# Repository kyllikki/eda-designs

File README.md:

EDA Designs
===========

Electronic designs under MIT licence unless stated differently in their directories.

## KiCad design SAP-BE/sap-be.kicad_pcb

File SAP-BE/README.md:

Simple As Possible (SAP) computer by Ben Eater
==============================================

This is a schematic capture of this project derived from the excellent video series [1]

The design belongs to Ben, I just made a schematic in kicad

This schematic is released under CC BY-SA licence

[1] https://www.youtube.com/watch?v=HyznrdDSSGM&list=PLowKtXNTBypGqImE405J2565dvjafglHU

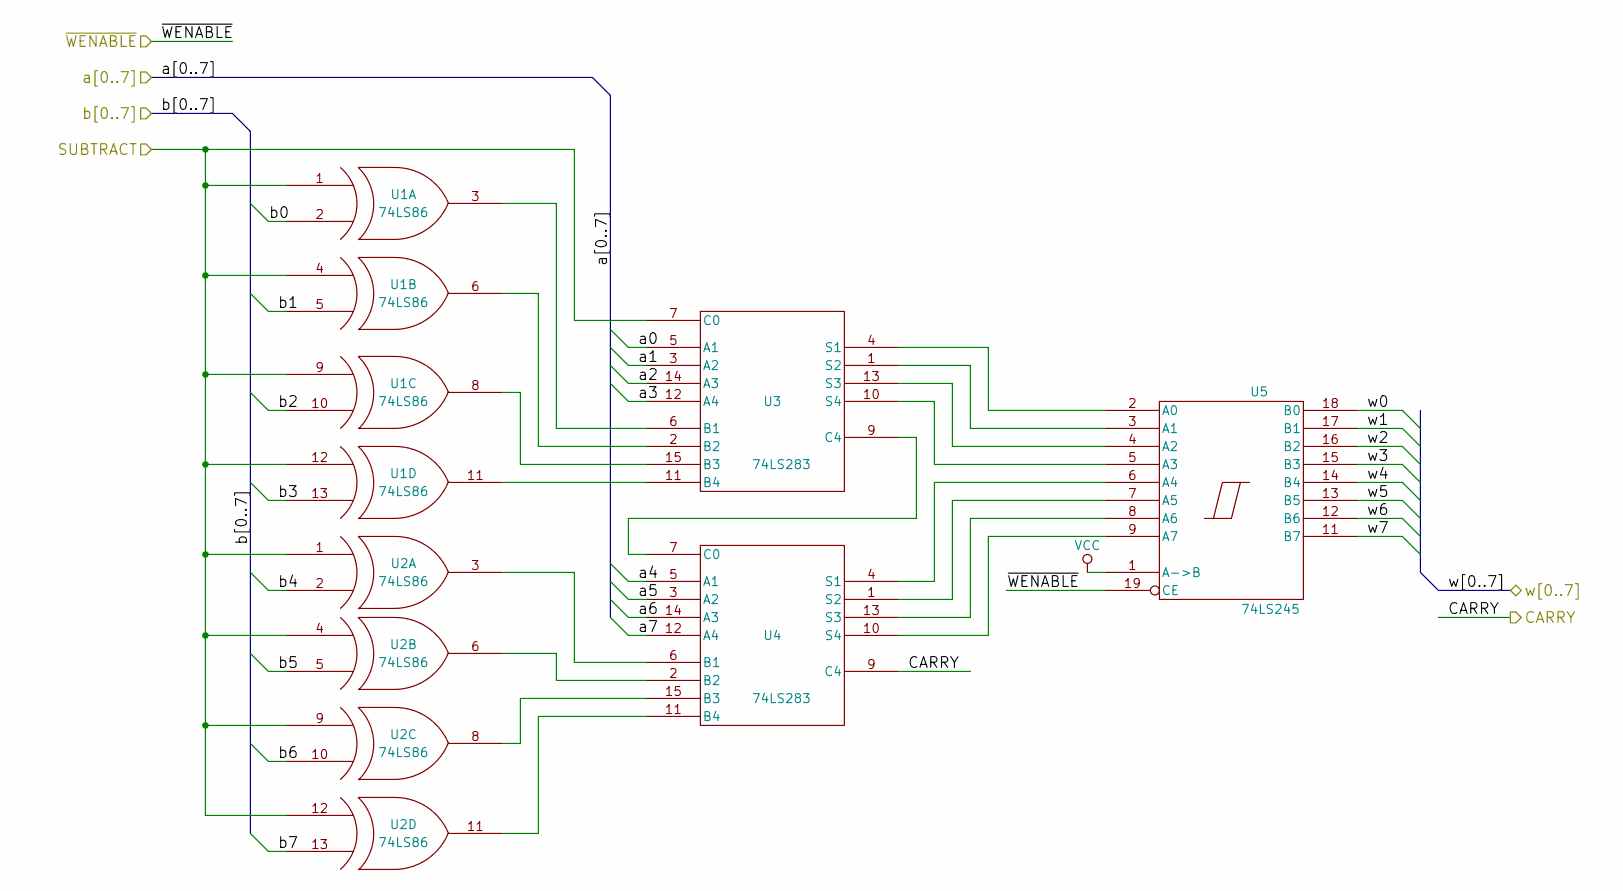
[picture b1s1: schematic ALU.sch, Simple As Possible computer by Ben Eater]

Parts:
U1, U2: 74LS86; DIP-14_W7.62mm_LongPads
U3, U4: 74LS283; DIP-16_W7.62mm_LongPads
U5: 74LS245; DIP-20_W7.62mm_LongPads

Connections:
/ALU/a0: U3.5 (A1); also elsewhere on the board
/ALU/a1: U3.3 (A2); also elsewhere on the board
/ALU/a2: U3.14 (A3); also elsewhere on the board
/ALU/a3: U3.12 (A4); also elsewhere on the board
/ALU/a4: U4.5 (A1); also elsewhere on the board
/ALU/a5: U4.3 (A2); also elsewhere on the board
/ALU/a6: U4.14 (A3); also elsewhere on the board
/ALU/a7: U4.12 (A4); also elsewhere on the board
/ALU/b0: U1.2 (IN2); also elsewhere on the board
/ALU/b1: U1.5 (IN2); also elsewhere on the board
/ALU/b2: U1.10 (IN2); also elsewhere on the board
/ALU/b3: U1.13 (IN2); also elsewhere on the board
/ALU/b4: U2.2 (IN2); also elsewhere on the board
/ALU/b5: U2.5 (IN2); also elsewhere on the board
/ALU/b6: U2.10 (IN2); also elsewhere on the board
/ALU/b7: U2.13 (IN2); also elsewhere on the board
/ALU/w2: U5.16 (B2); also elsewhere on the board
/ALU/w3: U5.15 (B3); also elsewhere on the board
/ALU/w4: U5.14 (B4); also elsewhere on the board
/ALU/w5: U5.13 (B5); also elsewhere on the board
/ALU/w6: U5.12 (B6); also elsewhere on the board
/ALU/w7: U5.11 (B7); also elsewhere on the board
/CY: U4.9 (C4); also elsewhere on the board
/SU: U1.1 (IN1), U1.4 (IN1), U1.9 (IN1), U1.12 (IN1), U2.1 (IN1), U2.4 (IN1), U2.9 (IN1), U2.12 (IN1), U3.7 (C0); also elsewhere on the board
unnamed: U1.3 (OUT), U3.6 (B1)
unnamed: U1.6 (OUT), U3.2 (B2)
unnamed: U1.8 (OUT), U3.15 (B3)
unnamed: U1.11 (OUT), U3.11 (B4)
unnamed: U2.3 (OUT), U4.6 (B1)
unnamed: U2.6 (OUT), U4.2 (B2)
unnamed: U2.8 (OUT), U4.15 (B3)
unnamed: U2.11 (OUT), U4.11 (B4)
unnamed: U3.1 (S2), U5.3 (A1)
unnamed: U3.4 (S1), U5.2 (A0)
unnamed: U3.9 (C4), U4.7 (C0)
unnamed: U3.10 (S4), U5.5 (A3)
unnamed: U3.13 (S3), U5.4 (A2)
unnamed: U4.1 (S2), U5.7 (A5)
unnamed: U4.4 (S1), U5.6 (A4)
unnamed: U4.10 (S4), U5.9 (A7)
unnamed: U4.13 (S3), U5.8 (A6)
VCC: U1.14 (VCC), U2.14 (VCC), U3.16 (VCC), U4.16 (VCC), U5.1 (A->B); also elsewhere on the board

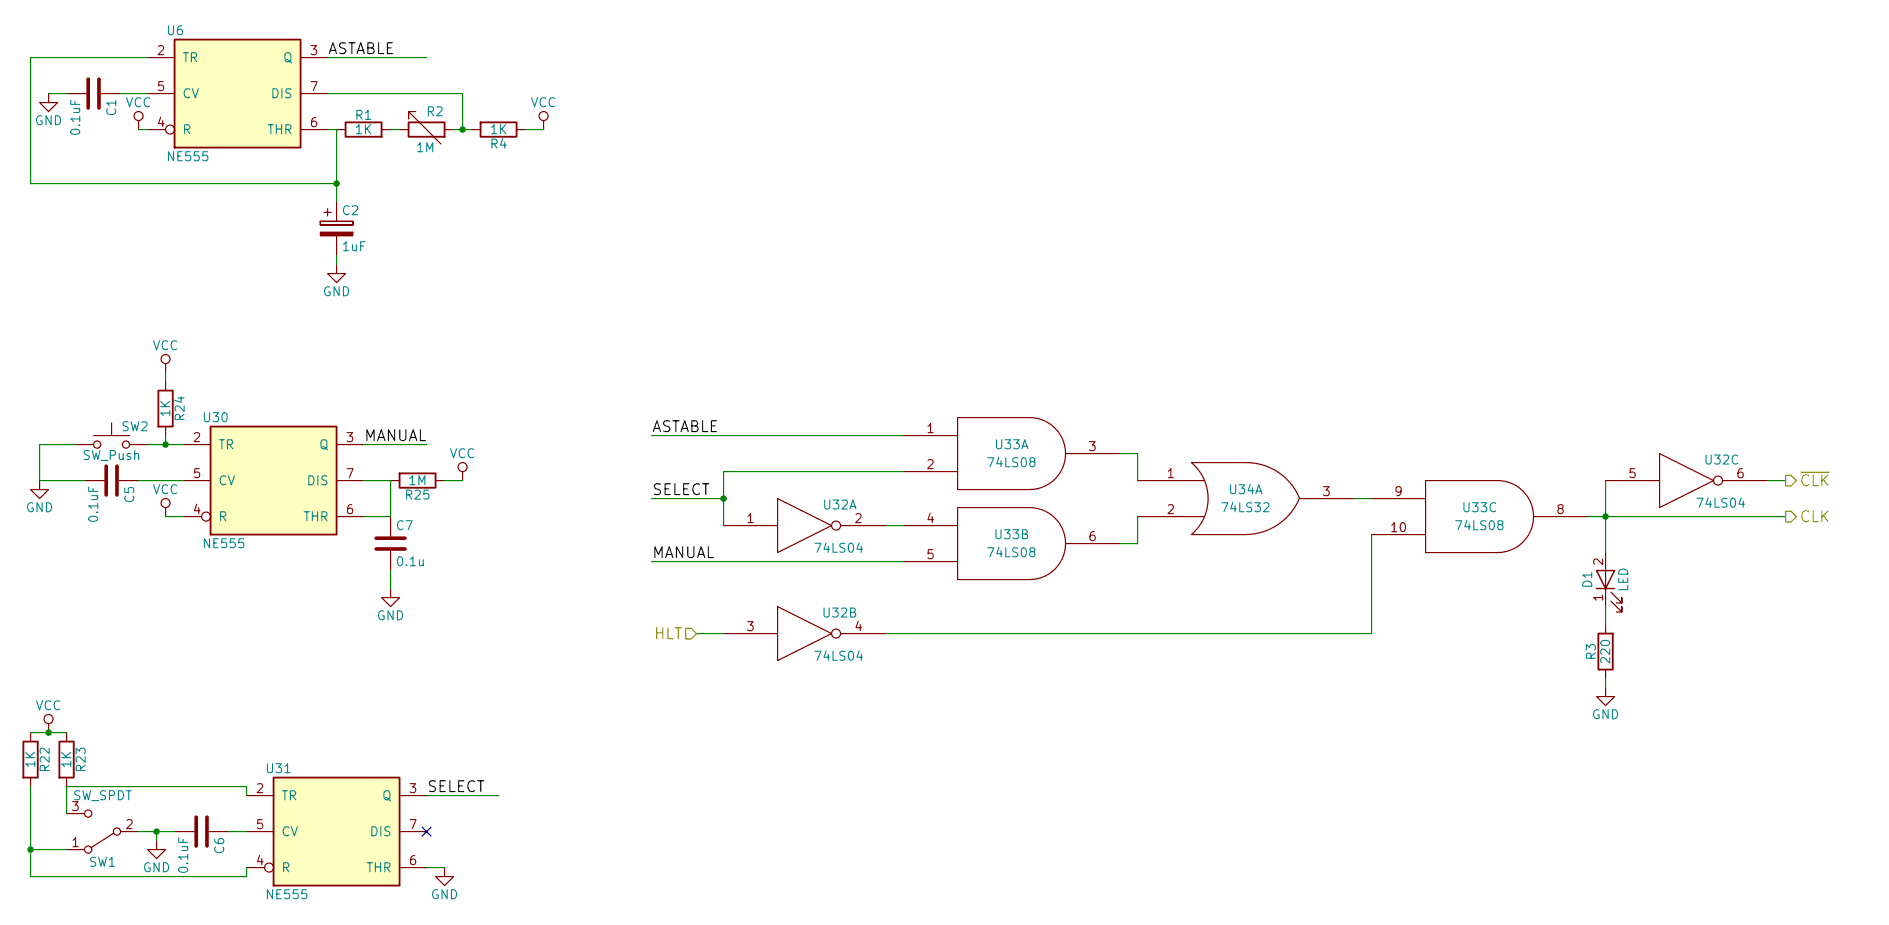
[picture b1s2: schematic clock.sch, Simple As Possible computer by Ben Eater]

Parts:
C1, C5, C6: 0.1uF; C_Disc_D6_P5
C2: 1uF; C_Radial_D5_L11_P2
C7: 0.1u; C_Disc_D6_P5
D1: LED; LED-5MM
R1, R4, R22, R23, R24: 1K; Resistor_Horizontal_RM7mm
R2: 1M; Potentiometer_Alps-RK16-single
R3: 220; Resistor_Horizontal_RM7mm
R25: 1M; Resistor_Horizontal_RM7mm
SW1: SW_SPDT; SW_Micro_SPST
SW2: SW_Push; SW_PUSH_6mm_h9.5mm
U6, U30, U31: NE555; DIP-8_W7.62mm_LongPads
U32: 74LS04; DIP-14_W7.62mm_LongPads
U33: 74LS08; DIP-14_W7.62mm_LongPads
U34: 74LS32; DIP-14_W7.62mm_LongPads

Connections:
/CLK: D1.2 (A), U32.5, U33.8; also elsewhere on the board
/HLT: U32.3; also elsewhere on the board
/clock/ASTABLE: U6.3 (Q), U33.1
/clock/MANUAL: U30.3 (Q), U33.5
/clock/SELECT: U31.3 (Q), U32.1, U33.2
/~CLK: U32.6; also elsewhere on the board
unnamed: C1.1, U6.5 (CV)
unnamed: C2.1, R1.1, U6.2 (TR), U6.6 (THR)
unnamed: C5.1, U30.5 (CV)
unnamed: C6.1, U31.5 (CV)
unnamed: C7.1, R25.2, U30.6 (THR), U30.7 (DIS)
unnamed: D1.1 (K), R3.2
unnamed: R1.2, R2.1
unnamed: R2.2, R4.2, U6.7 (DIS)
unnamed: R22.2, SW1.1 (A), U31.4 (R)
unnamed: R23.2, SW1.3 (C), U31.2 (TR)
unnamed: R24.2, SW2.2, U30.2 (TR)
unnamed: U32.2, U33.4
unnamed: U32.4, U33.10
unnamed: U33.3, U34.1
unnamed: U33.6, U34.2
unnamed: U33.9, U34.3
VCC: R4.1, R22.1, R23.1, R24.1, R25.1, U6.4 (R), U6.8 (VCC), U30.4 (R), U30.8 (VCC), U31.8 (VCC), U32.14 (VCC), U33.14 (VCC), U34.14 (VCC); also elsewhere on the board

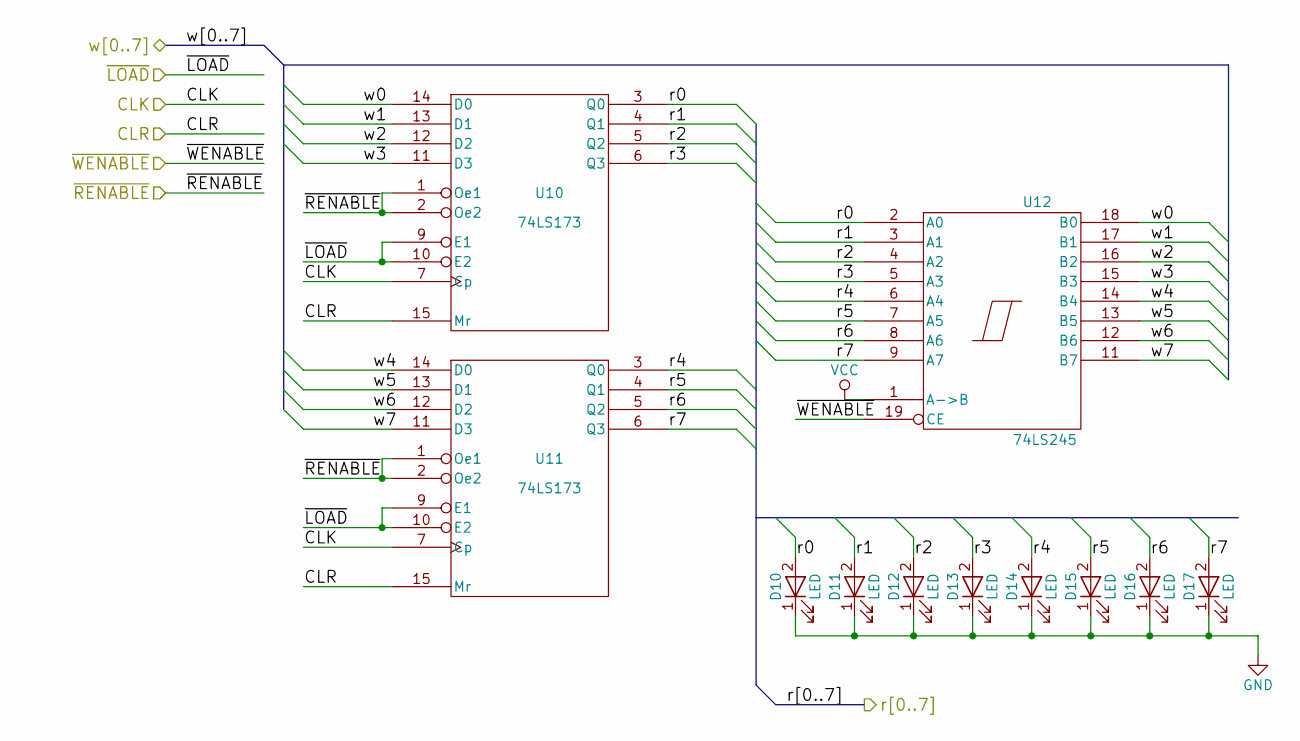
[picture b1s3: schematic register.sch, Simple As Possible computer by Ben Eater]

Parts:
D2, D3, D4, D5, D6, D7, D8, D9: LED; LED-5MM
U7, U8: 74LS173; DIP-16_W7.62mm_LongPads
U9: 74LS245; DIP-20_W7.62mm_LongPads

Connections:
/ALU/b0: D2.2 (A), U7.3 (Q0), U9.2 (A0); also elsewhere on the board
/ALU/b1: D3.2 (A), U7.4 (Q1), U9.3 (A1); also elsewhere on the board
/ALU/b2: D4.2 (A), U7.5 (Q2), U9.4 (A2); also elsewhere on the board
/ALU/b3: D5.2 (A), U7.6 (Q3), U9.5 (A3); also elsewhere on the board
/ALU/b4: D6.2 (A), U8.3 (Q0), U9.6 (A4); also elsewhere on the board
/ALU/b5: D7.2 (A), U8.4 (Q1), U9.7 (A5); also elsewhere on the board
/ALU/b6: D8.2 (A), U8.5 (Q2), U9.8 (A6); also elsewhere on the board
/ALU/b7: D9.2 (A), U8.6 (Q3), U9.9 (A7); also elsewhere on the board
/ALU/w0: U7.14 (D0), U9.18 (B0); also elsewhere on the board
/ALU/w1: U7.13 (D1), U9.17 (B1); also elsewhere on the board
/ALU/w2: U7.12 (D2), U9.16 (B2); also elsewhere on the board
/ALU/w3: U7.11 (D3), U9.15 (B3); also elsewhere on the board
/ALU/w4: U8.14 (D0), U9.14 (B4); also elsewhere on the board
/ALU/w5: U8.13 (D1), U9.13 (B5); also elsewhere on the board
/ALU/w6: U8.12 (D2), U9.12 (B6); also elsewhere on the board
/ALU/w7: U8.11 (D3), U9.11 (B7); also elsewhere on the board
/CLK: U7.7 (Cp), U8.7 (Cp); also elsewhere on the board
/~BI: U7.9 (E1), U7.10 (E2), U8.9 (E1), U8.10 (E2); also elsewhere on the board
VCC: U9.1 (A->B); also elsewhere on the board

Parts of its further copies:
D10, D11, D12, D13, D14, D15, D16, D17: LED; LED-5MM
U10, U11: 74LS173; DIP-16_W7.62mm_LongPads
U12: 74LS245; DIP-20_W7.62mm_LongPads

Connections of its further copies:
/ALU/a0: D10.2 (A), U10.3 (Q0), U12.2 (A0); also elsewhere on the board
/ALU/a1: D11.2 (A), U10.4 (Q1), U12.3 (A1); also elsewhere on the board
/ALU/a2: D12.2 (A), U10.5 (Q2), U12.4 (A2); also elsewhere on the board
/ALU/a3: D13.2 (A), U10.6 (Q3), U12.5 (A3); also elsewhere on the board
/ALU/a4: D14.2 (A), U11.3 (Q0), U12.6 (A4); also elsewhere on the board
/ALU/a5: D15.2 (A), U11.4 (Q1), U12.7 (A5); also elsewhere on the board
/ALU/a6: D16.2 (A), U11.5 (Q2), U12.8 (A6); also elsewhere on the board
/ALU/a7: D17.2 (A), U11.6 (Q3); also elsewhere on the board
/ALU/w0: U10.14 (D0); also elsewhere on the board
/ALU/w1: U10.13 (D1); also elsewhere on the board
/ALU/w2: U10.12 (D2); also elsewhere on the board
/ALU/w3: U10.11 (D3); also elsewhere on the board
/ALU/w4: U11.14 (D0); also elsewhere on the board
/ALU/w5: U11.13 (D1); also elsewhere on the board
/ALU/w6: U11.12 (D2); also elsewhere on the board
/ALU/w7: U11.11 (D3); also elsewhere on the board
/CLK: U10.7 (Cp), U11.7 (Cp); also elsewhere on the board
/~AI: U10.9 (E1), U10.10 (E2), U11.9 (E1), U11.10 (E2); also elsewhere on the board
VCC: U10.16 (VCC), U11.16 (VCC), U12.1 (A->B); also elsewhere on the board

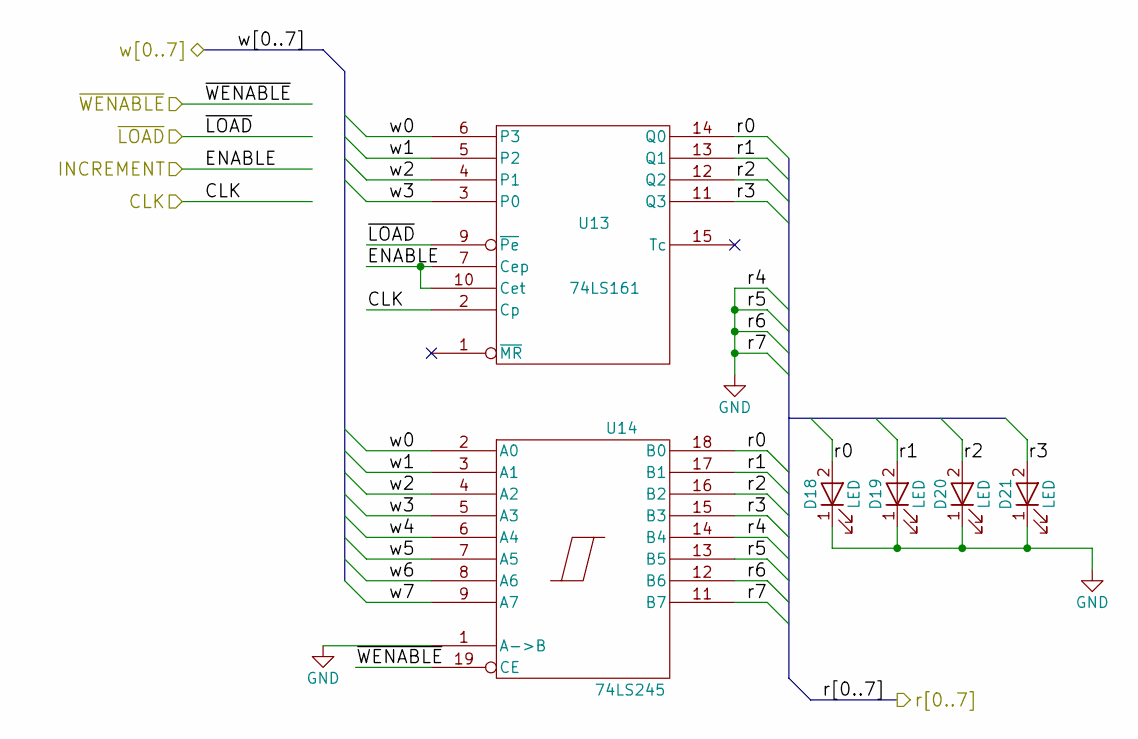
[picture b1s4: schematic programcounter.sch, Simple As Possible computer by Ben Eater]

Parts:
D18, D19, D20, D21: LED; LED-5MM
U13: 74LS161; DIP-16_W7.62mm_LongPads
U14: 74LS245; DIP-20_W7.62mm_LongPads

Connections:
/ALU/w0: U13.6 (P3), U14.2 (A0); also elsewhere on the board
/ALU/w1: U13.5 (P2), U14.3 (A1); also elsewhere on the board
/ALU/w2: U13.4 (P1), U14.4 (A2); also elsewhere on the board
/ALU/w3: U13.3 (P0), U14.5 (A3); also elsewhere on the board
/ALU/w4: U14.6 (A4); also elsewhere on the board
/ALU/w5: U14.7 (A5); also elsewhere on the board
/ALU/w6: U14.8 (A6); also elsewhere on the board
/ALU/w7: U14.9 (A7); also elsewhere on the board
/CE: U13.7 (Cep), U13.10 (Cet); also elsewhere on the board
/CLK: U13.2 (Cp); also elsewhere on the board
/PC/r0: D18.2 (A), U13.14 (Q0), U14.18 (B0)
/PC/r1: D19.2 (A), U13.13 (Q1), U14.17 (B1)
/PC/r2: D20.2 (A), U13.12 (Q2), U14.16 (B2)
/PC/r3: D21.2 (A), U13.11 (Q3), U14.15 (B3)
/~CO: U14.19 (CE); also elsewhere on the board
/~J: U13.9 (~Pe); also elsewhere on the board
VCC: U13.16 (VCC), U14.20 (VCC); also elsewhere on the board

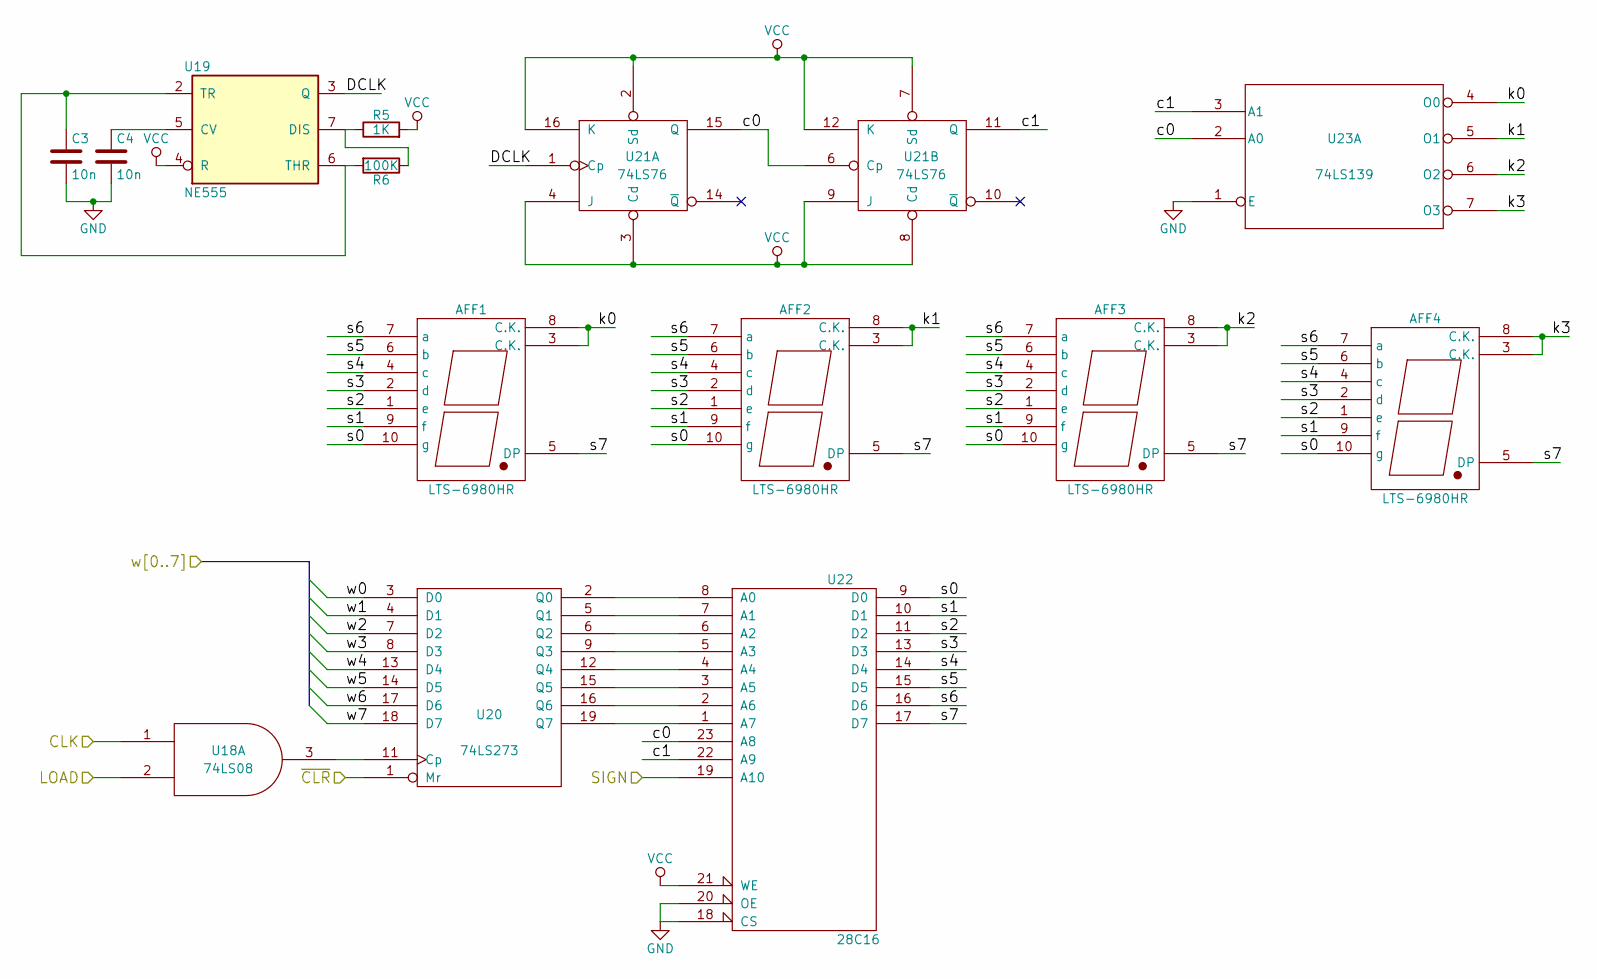
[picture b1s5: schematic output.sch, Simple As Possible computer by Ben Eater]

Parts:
AFF1, AFF2, AFF3, AFF4: LTS-6980HR; 7SegmentLED_LTS6760_LTS6780
C3, C4: 10n; C_Disc_D6_P5
R5: 1K; Resistor_Horizontal_RM7mm
R6: 100K; Resistor_Horizontal_RM7mm
U18: 74LS08; DIP-14_W7.62mm_LongPads
U19: NE555; DIP-8_W7.62mm_LongPads
U20: 74LS273; DIP-20_W7.62mm_LongPads
U21: 74LS76; DIP-16_W7.62mm_LongPads
U22: 28C16; DIP-24_W15.24mm_LongPads
U23: 74LS139; DIP-16_W7.62mm_LongPads

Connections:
/ALU/w0: U20.3 (D0); also elsewhere on the board
/ALU/w1: U20.4 (D1); also elsewhere on the board
/ALU/w2: U20.7 (D2); also elsewhere on the board
/ALU/w3: U20.8 (D3); also elsewhere on the board
/ALU/w4: U20.13 (D4); also elsewhere on the board
/ALU/w5: U20.14 (D5); also elsewhere on the board
/ALU/w6: U20.17 (D6); also elsewhere on the board
/ALU/w7: U20.18 (D7); also elsewhere on the board
/CLK: U18.1; also elsewhere on the board
/OI: U18.2; also elsewhere on the board
/output/DCLK: U19.3 (Q), U21.1 (Cp)
/output/c0: U21.6 (Cp), U21.15 (Q), U22.23 (A8), U23.2 (A0)
/output/c1: U21.11 (Q), U22.22 (A9), U23.3 (A1)
/output/k0: AFF1.3 (C.K.), AFF1.8 (C.K.), U23.4 (O0)
/output/k1: AFF2.3 (C.K.), AFF2.8 (C.K.), U23.5 (O1)
/output/k2: AFF3.3 (C.K.), AFF3.8 (C.K.), U23.6 (O2)
/output/k3: AFF4.3 (C.K.), AFF4.8 (C.K.), U23.7 (O3)
/output/s0: AFF1.10 (g), AFF2.10 (g), AFF3.10 (g), AFF4.10 (g), U22.9 (D0)
/output/s1: AFF1.9 (f), AFF2.9 (f), AFF3.9 (f), AFF4.9 (f), U22.10 (D1)
/output/s2: AFF1.1 (e), AFF2.1 (e), AFF3.1 (e), AFF4.1 (e), U22.11 (D2)
/output/s3: AFF1.2 (d), AFF2.2 (d), AFF3.2 (d), AFF4.2 (d), U22.13 (D3)
/output/s4: AFF1.4 (c), AFF2.4 (c), AFF3.4 (c), AFF4.4 (c), U22.14 (D4)
/output/s5: AFF1.6 (b), AFF2.6 (b), AFF3.6 (b), AFF4.6 (b), U22.15 (D5)
/output/s6: AFF1.7 (a), AFF2.7 (a), AFF3.7 (a), AFF4.7 (a), U22.16 (D6)
/output/s7: AFF1.5 (DP), AFF2.5 (DP), AFF3.5 (DP), AFF4.5 (DP), U22.17 (D7)
unnamed: C3.1, R6.2, U19.2 (TR), U19.6 (THR)
unnamed: C4.1, U19.5 (CV)
unnamed: R5.1, R6.1, U19.7 (DIS)
unnamed: U18.3, U20.11 (Cp)
unnamed: U20.2 (Q0), U22.8 (A0)
unnamed: U20.5 (Q1), U22.7 (A1)
unnamed: U20.6 (Q2), U22.6 (A2)
unnamed: U20.9 (Q3), U22.5 (A3)
unnamed: U20.12 (Q4), U22.4 (A4)
unnamed: U20.15 (Q5), U22.3 (A5)
unnamed: U20.16 (Q6), U22.2 (A6)
unnamed: U20.19 (Q7), U22.1 (A7)
VCC: R5.2, U18.14 (VCC), U19.4 (R), U19.8 (VCC), U20.1 (Mr), U20.20 (VCC), U21.2 (Sd), U21.3 (Cd), U21.4 (J), U21.5 (VCC), U21.7 (Sd), U21.8 (Cd), U21.9 (J), U21.12 (K), U21.16 (K), U22.21 (WE), U22.24 (VCC), U23.16 (VCC); also elsewhere on the board

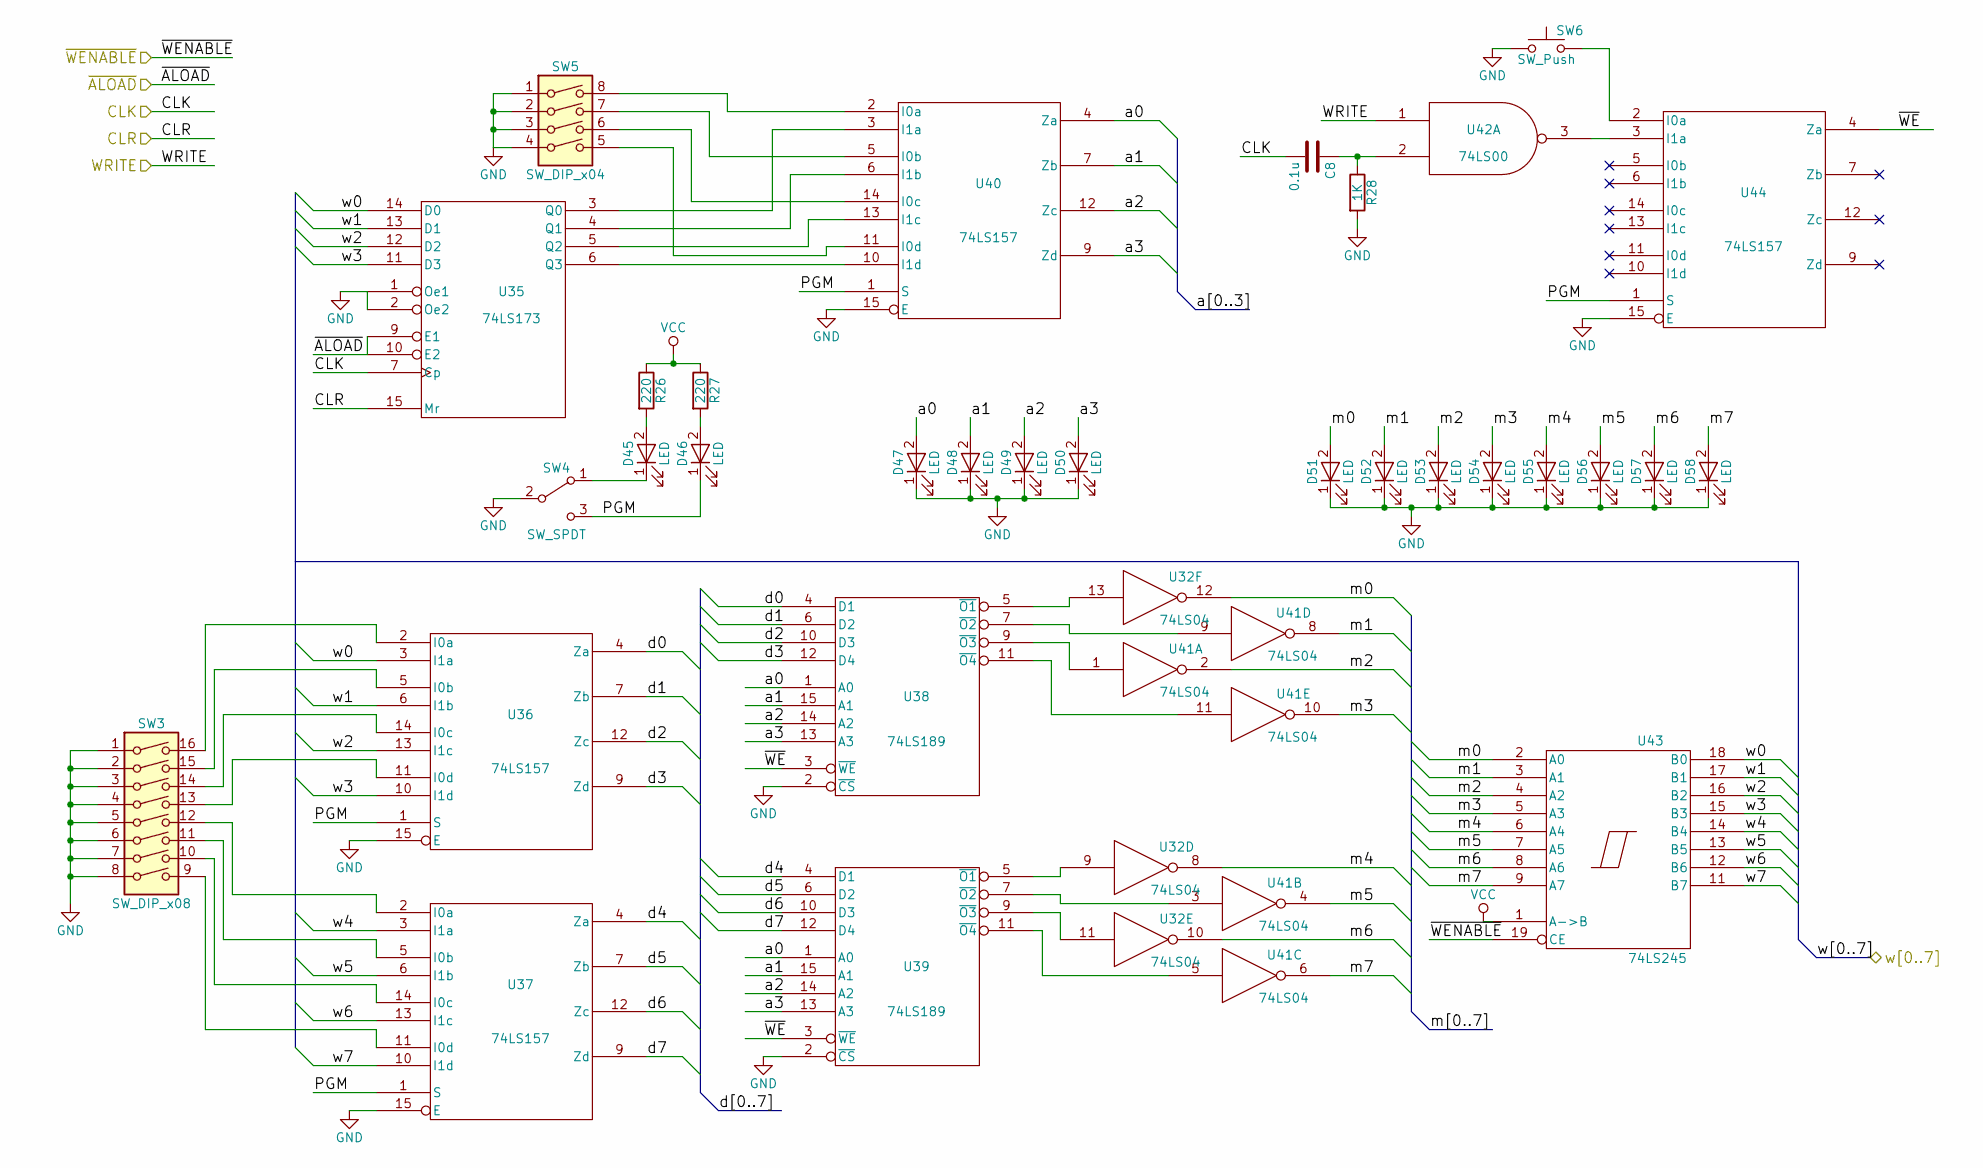
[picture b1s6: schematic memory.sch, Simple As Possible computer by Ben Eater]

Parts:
C8: 0.1u; C_Disc_D6_P5
D45, D46, D47, D48, D49, D50, D51, D52, D53, D54, D55, D56, D57, D58: LED; LED-5MM
R26, R27: 220; Resistor_Horizontal_RM7mm
R28: 1K; Resistor_Horizontal_RM7mm
SW3: SW_DIP_x08; SW_DIP_x8_Slide
SW4: SW_SPDT; SW_Micro_SPST
SW5: SW_DIP_x04; SW_DIP_x4_Slide
SW6: SW_Push; SW_PUSH_6mm_h9.5mm
U32, U41: 74LS04; DIP-14_W7.62mm_LongPads
U35: 74LS173; DIP-16_W7.62mm_LongPads
U36, U37, U40, U44: 74LS157; DIP-16_W7.62mm_LongPads
U38, U39: 74LS189; DIP-16_W7.62mm_LongPads
U42: 74LS00; DIP-14_W7.62mm_LongPads
U43: 74LS245; DIP-20_W7.62mm_LongPads

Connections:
/ALU/w0: U35.14 (D0), U36.3 (I1a), U43.18 (B0); also elsewhere on the board
/ALU/w1: U35.13 (D1), U36.6 (I1b), U43.17 (B1); also elsewhere on the board
/ALU/w2: U35.12 (D2), U36.13 (I1c), U43.16 (B2); also elsewhere on the board
/ALU/w3: U35.11 (D3), U36.10 (I1d), U43.15 (B3); also elsewhere on the board
/ALU/w4: U37.3 (I1a), U43.14 (B4); also elsewhere on the board
/ALU/w5: U37.6 (I1b), U43.13 (B5); also elsewhere on the board
/ALU/w6: U37.13 (I1c), U43.12 (B6); also elsewhere on the board
/ALU/w7: U37.10 (I1d), U43.11 (B7); also elsewhere on the board
/CLK: C8.2, U35.7 (Cp); also elsewhere on the board
/RI: U42.1; also elsewhere on the board
/memory/PGM: D46.1 (K), SW4.3 (C), U36.1 (S), U37.1 (S), U40.1 (S), U44.1 (S)
/memory/a0: D47.2 (A), U38.1 (A0), U39.1 (A0), U40.4 (Za)
/memory/a1: D48.2 (A), U38.15 (A1), U39.15 (A1), U40.7 (Zb)
/memory/a2: D49.2 (A), U38.14 (A2), U39.14 (A2), U40.12 (Zc)
/memory/a3: D50.2 (A), U38.13 (A3), U39.13 (A3), U40.9 (Zd)
/memory/d0: U36.4 (Za), U38.4 (D1)
/memory/d1: U36.7 (Zb), U38.6 (D2)
/memory/d2: U36.12 (Zc), U38.10 (D3)
/memory/d3: U36.9 (Zd), U38.12 (D4)
/memory/d4: U37.4 (Za), U39.4 (D1)
/memory/d5: U37.7 (Zb), U39.6 (D2)
/memory/d6: U37.12 (Zc), U39.10 (D3)
/memory/d7: U37.9 (Zd), U39.12 (D4)
/memory/m0: D51.2 (A), U32.12, U43.2 (A0)
/memory/m1: D52.2 (A), U41.8, U43.3 (A1)
/memory/m2: D53.2 (A), U41.2, U43.4 (A2)
/memory/m3: D54.2 (A), U41.10, U43.5 (A3)
/memory/m4: D55.2 (A), U32.8, U43.6 (A4)
/memory/m5: D56.2 (A), U41.4, U43.7 (A5)
/memory/m6: D57.2 (A), U32.10, U43.8 (A6)
/memory/m7: D58.2 (A), U41.6, U43.9 (A7)
/memory/~WE: U38.3 (~WE), U39.3 (~WE), U44.4 (Za)
/~MI: U35.9 (E1), U35.10 (E2); also elsewhere on the board
/~RO: U43.19 (CE); also elsewhere on the board
unnamed: C8.1, R28.1, U42.2
unnamed: D45.1 (K), SW4.1 (A)
unnamed: D45.2 (A), R26.2
unnamed: D46.2 (A), R27.2
unnamed: SW3.9, U37.11 (I0d)
unnamed: SW3.10, U37.14 (I0c)
unnamed: SW3.11, U37.5 (I0b)
unnamed: SW3.12, U37.2 (I0a)
unnamed: SW3.13, U36.11 (I0d)
unnamed: SW3.14, U36.14 (I0c)
unnamed: SW3.15, U36.5 (I0b)
unnamed: SW3.16, U36.2 (I0a)
unnamed: SW5.5, U40.11 (I0d)
unnamed: SW5.6, U40.14 (I0c)
unnamed: SW5.7, U40.5 (I0b)
unnamed: SW5.8, U40.2 (I0a)
unnamed: SW6.2, U44.2 (I0a)
unnamed: U32.9, U39.5 (~O1)
unnamed: U32.11, U39.9 (~O3)
unnamed: U32.13, U38.5 (~O1)
unnamed: U35.3 (Q0), U40.3 (I1a)
unnamed: U35.4 (Q1), U40.6 (I1b)
unnamed: U35.5 (Q2), U40.13 (I1c)
unnamed: U35.6 (Q3), U40.10 (I1d)
unnamed: U38.7 (~O2), U41.9
unnamed: U38.9 (~O3), U41.1
unnamed: U38.11 (~O4), U41.11
unnamed: U39.7 (~O2), U41.3
unnamed: U39.11 (~O4), U41.5
unnamed: U42.3, U44.3 (I1a)
VCC: R26.1, R27.1, U32.14 (VCC), U35.16 (VCC), U36.16 (VCC), U37.16 (VCC), U38.16 (VCC), U39.16 (VCC), U40.16 (VCC), U41.14 (VCC), U42.14 (VCC), U43.1 (A->B), U43.20 (VCC), U44.16 (VCC); also elsewhere on the board

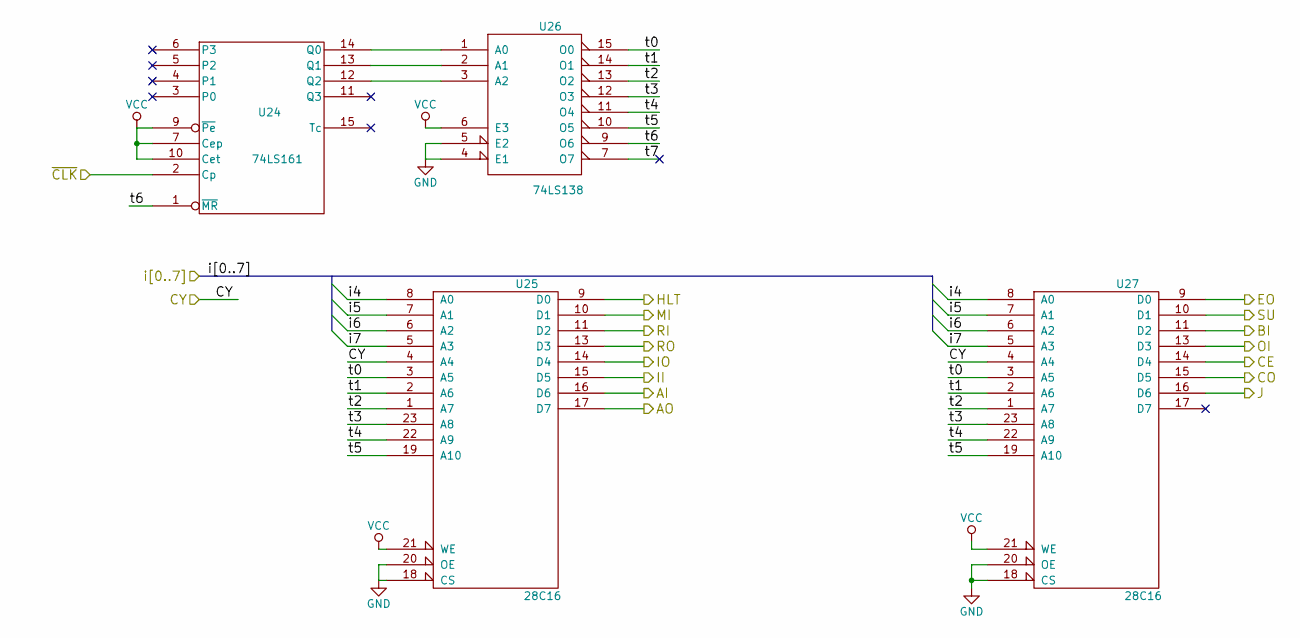
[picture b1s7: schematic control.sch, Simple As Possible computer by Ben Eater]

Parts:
U24: 74LS161; DIP-16_W7.62mm_LongPads
U25, U27: 28C16; DIP-24_W15.24mm_LongPads
U26: 74LS138; DIP-16_W7.62mm_LongPads

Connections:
/AI: U25.16 (D6); also elsewhere on the board
/AO: U25.17 (D7); also elsewhere on the board
/BI: U27.11 (D2); also elsewhere on the board
/CE: U27.14 (D4); also elsewhere on the board
/CO: U27.15 (D5); also elsewhere on the board
/CY: U25.4 (A4), U27.4 (A4); also elsewhere on the board
/EO: U27.9 (D0); also elsewhere on the board
/HLT: U25.9 (D0); also elsewhere on the board
/II: U25.15 (D5); also elsewhere on the board
/IO: U25.14 (D4); also elsewhere on the board
/J: U27.16 (D6); also elsewhere on the board
/MI: U25.10 (D1); also elsewhere on the board
/OI: U27.13 (D3); also elsewhere on the board
/RI: U25.11 (D2); also elsewhere on the board
/RO: U25.13 (D3); also elsewhere on the board
/SU: U27.10 (D1); also elsewhere on the board
/control/t0: U25.3 (A5), U26.15 (O0), U27.3 (A5)
/control/t1: U25.2 (A6), U26.14 (O1), U27.2 (A6)
/control/t2: U25.1 (A7), U26.13 (O2), U27.1 (A7)
/control/t3: U25.23 (A8), U26.12 (O3), U27.23 (A8)
/control/t4: U25.22 (A9), U26.11 (O4), U27.22 (A9)
/control/t5: U25.19 (A10), U26.10 (O5), U27.19 (A10)
/control/t6: U24.1 (~MR), U26.9 (O6)
/control/t7: U26.7 (O7)
/~CLK: U24.2 (Cp); also elsewhere on the board
unnamed: U24.12 (Q2), U26.3 (A2)
unnamed: U24.13 (Q1), U26.2 (A1)
unnamed: U24.14 (Q0), U26.1 (A0)
VCC: U24.7 (Cep), U24.9 (~Pe), U24.10 (Cet), U24.16 (VCC), U25.21 (WE), U25.24 (VCC), U26.6 (E3), U26.16 (VCC), U27.21 (WE), U27.24 (VCC); also elsewhere on the board

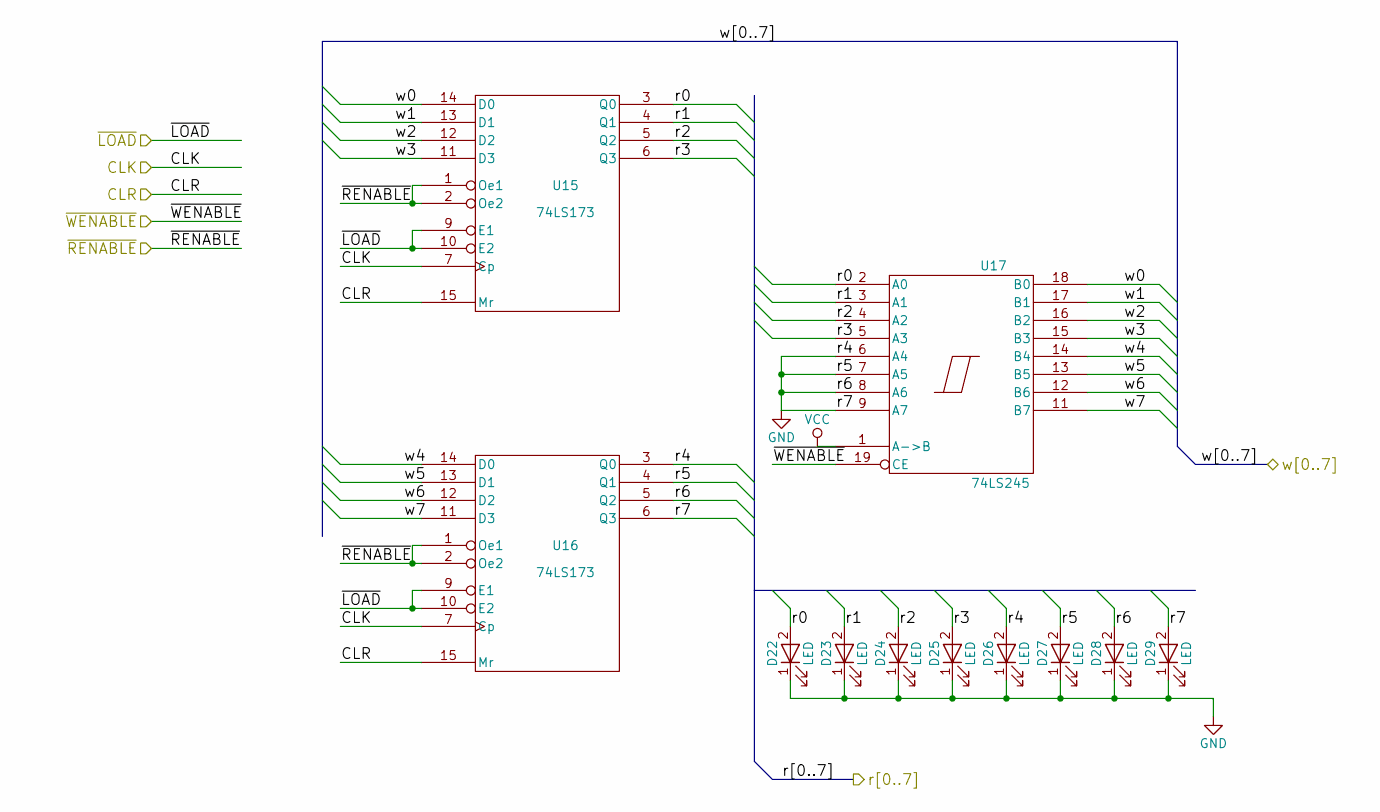
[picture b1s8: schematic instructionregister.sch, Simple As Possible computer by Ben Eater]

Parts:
D22, D23, D24, D25, D26, D27, D28, D29: LED; LED-5MM
U15, U16: 74LS173; DIP-16_W7.62mm_LongPads
U17: 74LS245; DIP-20_W7.62mm_LongPads

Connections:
/ALU/w0: U15.14 (D0), U17.18 (B0); also elsewhere on the board
/ALU/w1: U15.13 (D1), U17.17 (B1); also elsewhere on the board
/ALU/w2: U15.12 (D2), U17.16 (B2); also elsewhere on the board
/ALU/w3: U15.11 (D3), U17.15 (B3); also elsewhere on the board
/ALU/w4: U16.14 (D0), U17.14 (B4); also elsewhere on the board
/ALU/w5: U16.13 (D1), U17.13 (B5); also elsewhere on the board
/ALU/w6: U16.12 (D2), U17.12 (B6); also elsewhere on the board
/ALU/w7: U16.11 (D3), U17.11 (B7); also elsewhere on the board
/CLK: U15.7 (Cp), U16.7 (Cp); also elsewhere on the board
/IR/r0: D22.2 (A), U15.3 (Q0), U17.2 (A0)
/IR/r1: D23.2 (A), U15.4 (Q1), U17.3 (A1)
/IR/r2: D24.2 (A), U15.5 (Q2), U17.4 (A2)
/IR/r3: D25.2 (A), U15.6 (Q3), U17.5 (A3)
/~II: U15.9 (E1), U15.10 (E2), U16.9 (E1), U16.10 (E2); also elsewhere on the board
/~IO: U17.19 (CE); also elsewhere on the board
VCC: U15.16 (VCC), U16.16 (VCC), U17.1 (A->B), U17.20 (VCC); also elsewhere on the board

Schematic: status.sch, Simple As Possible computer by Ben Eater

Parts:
D30, D31, D32, D33, D34, D35, D36, D37, D38, D39, D40, D41, D42, D43, D44: LED; LED-5MM
R7, R8, R9, R10, R11, R12, R13, R14, R15, R16, R17, R18, R19, R20, R21: 470; Resistor_Horizontal_RM7mm
U28, U29: 74HC04; DIP-14_W7.62mm_LongPads

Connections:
/AI: D31.2 (A), U28.1; also elsewhere on the board
/AO: D34.2 (A), U28.5; also elsewhere on the board
/BI: D42.2 (A), U29.9; also elsewhere on the board
/CE: D32.2 (A); also elsewhere on the board
/CO: D35.2 (A), U28.9; also elsewhere on the board
/EO: D37.2 (A), U28.11; also elsewhere on the board
/HLT: D30.2 (A); also elsewhere on the board
/II: D43.2 (A), U29.13; also elsewhere on the board
/IO: D41.2 (A), U29.5; also elsewhere on the board
/J: D38.2 (A), U28.13; also elsewhere on the board
/MI: D33.2 (A), U28.3; also elsewhere on the board
/OI: D44.2 (A); also elsewhere on the board
/RI: D36.2 (A); also elsewhere on the board
/RO: D39.2 (A), U29.1; also elsewhere on the board
/SU: D40.2 (A); also elsewhere on the board
/~AI: U28.2; also elsewhere on the board
/~AO: U28.6
/~BI: U29.8; also elsewhere on the board
/~CO: U28.8; also elsewhere on the board
/~EO: U28.10
/~II: U29.12; also elsewhere on the board
/~IO: U29.6; also elsewhere on the board
/~J: U28.12; also elsewhere on the board
/~MI: U28.4; also elsewhere on the board
/~RO: U29.2; also elsewhere on the board
unnamed: D30.1 (K), R7.1
unnamed: D31.1 (K), R8.1
unnamed: D32.1 (K), R9.1
unnamed: D33.1 (K), R10.1
unnamed: D34.1 (K), R11.1
unnamed: D35.1 (K), R12.1
unnamed: D36.1 (K), R13.1
unnamed: D37.1 (K), R14.1
unnamed: D38.1 (K), R15.1
unnamed: D39.1 (K), R16.1
unnamed: D40.1 (K), R17.1
unnamed: D41.1 (K), R18.1
unnamed: D42.1 (K), R19.1
unnamed: D43.1 (K), R20.1
unnamed: D44.1 (K), R21.1
VCC: U28.14 (VCC), U29.14 (VCC); also elsewhere on the board

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
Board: 2 copper layers, 148 parts (0 on the bottom side), 200 nets, no tracks yet.

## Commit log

2017-05-10 add schematic capture of Simple As Possible computer by Ben Eater
2017-05-22 update control sheet to match video series
2017-05-29 Update with changes for reset
2017-05-30 add alternate SAP register designs
2018-04-09 Microcode EPROM A7 used as bank select
2018-04-09 Update with conditional flags
2018-04-13 add missing flags schematic sheet
2018-04-13 fixup flags schematic settings
2018-04-13 Improve memory schematic layout
2018-04-14 clean up memory module schematic a bit
2018-04-14 add bugfixed version

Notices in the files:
SAP-BE-BUGFIX/ALU.sch:
Schematic released as CC BY-SA
